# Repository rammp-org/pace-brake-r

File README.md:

# pace-brake-r
brake resistor circuit for protecting DC batteries on high power motor controllers

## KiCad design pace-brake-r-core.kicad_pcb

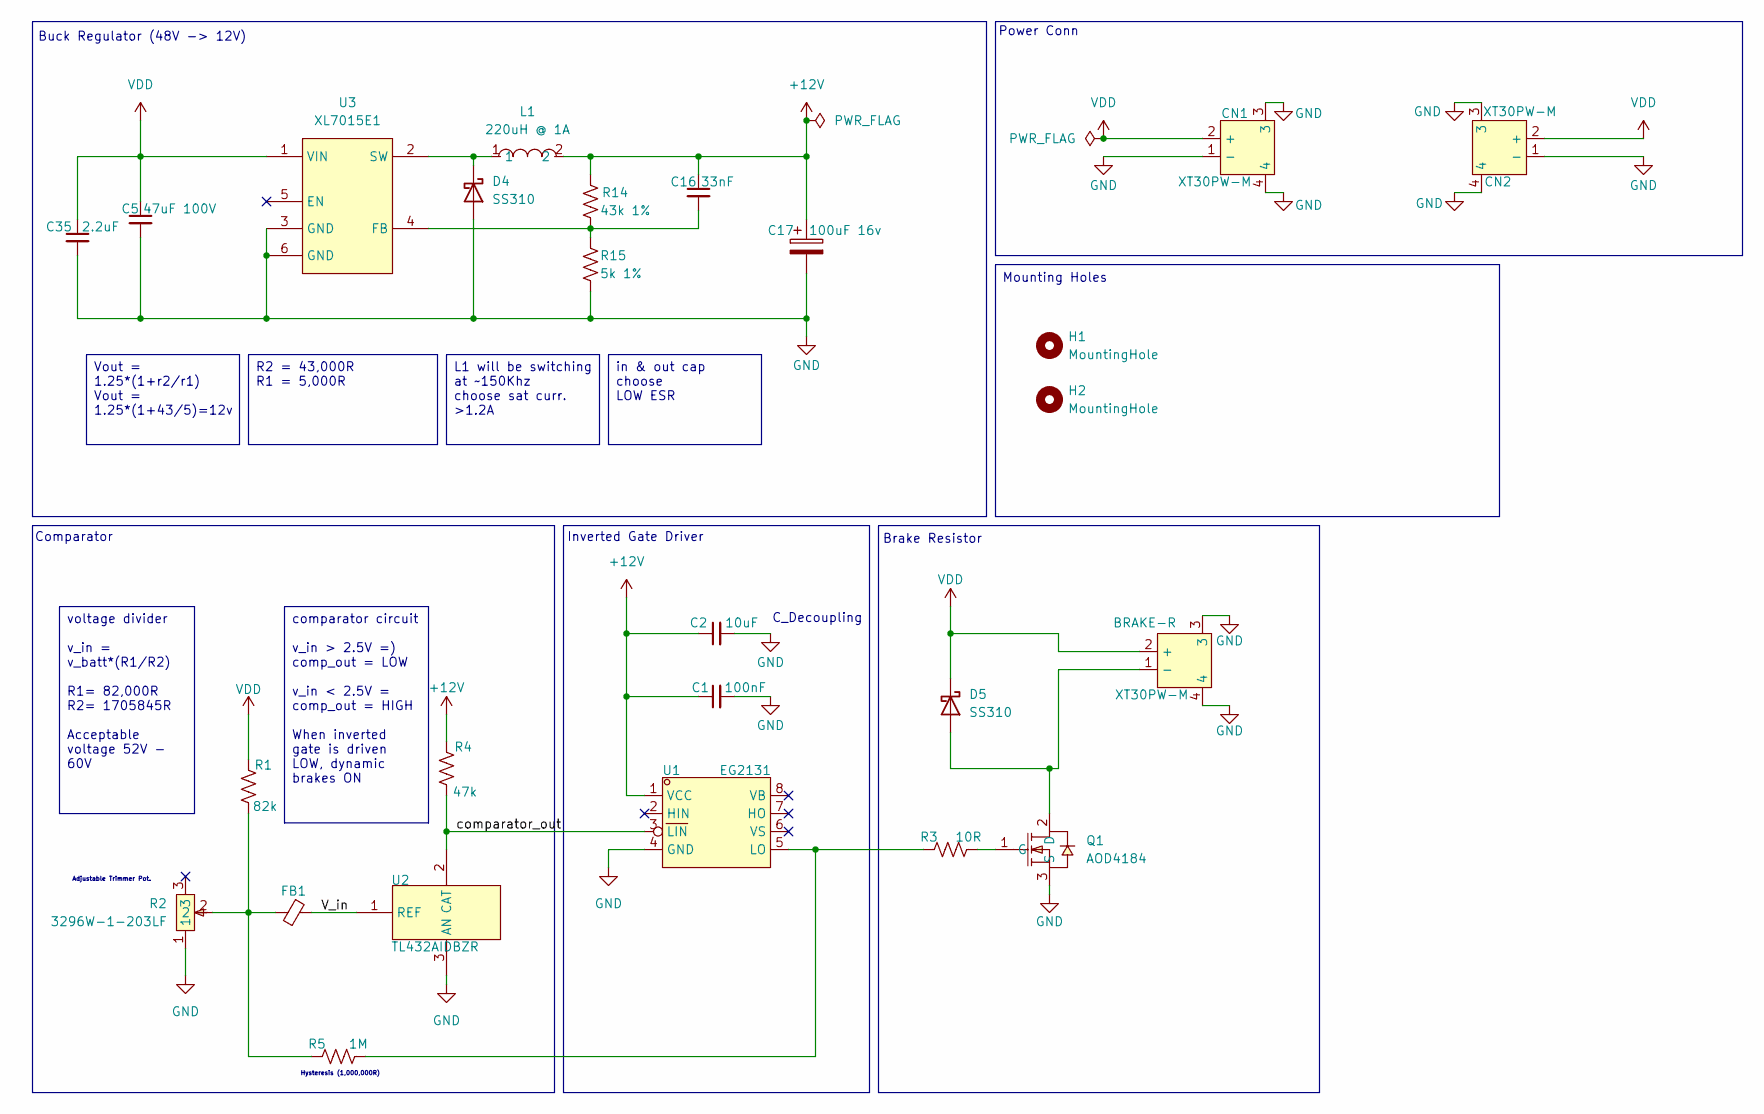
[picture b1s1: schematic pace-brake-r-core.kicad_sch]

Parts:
BRAKE-R: XT30PW-M; CONN-TH_XT30PW-M; MPN XT30PW-M30.G.Y; LCSC Part C431092
C1: 100nF; C_0402_1005Metric
C2: 10uF; C_0402_1005Metric
C5: 47uF 100V; CP_Elec_10x10
C16: 33nF; C_0402_1005Metric
C17: 100uF 16v; C_Elec_6.3x7.7; MPN EEEFPV101XAP; LCSC part C178585
C35: 2.2uF; C_1210_3225Metric
CN1, CN2: XT30PW-M; CONN-TH_XT30PW-M; MPN XT30PW-M30.G.Y; LCSC Part C431092
D4, D5: SS310; D_SMA
FB1: FerriteBead_Small; L0603
H1, H2: MountingHole; MountingHole_3.2mm_M3
L1: 220uH @ 1A; IND-TH_BD9.0-P5.00-D0.7; MPN RLB9012-221KL; LCSC Part C1330811
Q1: AOD4184; TO-252-2_L6.6-W6.1-P4.58-LS9.9-BR; MPN AOD4184-VB; LCSC Part C879026
R1: 82k; R_0402_1005Metric
R2: 3296W-1-203LF; RES-ADJ-TH_3P-L10.0-W10.0-P2.50-BL-BS; MPN 3296W-1-203LF; LCSC Part C34845
R3: 10R; R_0402_1005Metric
R4: 47k; R_0402_1005Metric
R5: 1M; R_0402_1005Metric
R14: 43k 1%; R_0402_1005Metric
R15: 5k 1%; R_0402_1005Metric
U1: EG2131; SOIC-8_L5.0-W4.0-P1.27-LS6.0-BL; MPN EG2131; LCSC Part C193777
U2: TL432AIDBZR; SOT-23-3_L2.9-W1.3-P1.90-LS2.4-BR; MPN TL432AIDBZR; LCSC Part C82720
U3: XL7015E1; TO-252-5_L6.6-W5.8-P1.27-TL; MPN XL7015E1; LCSC Part C73013

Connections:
+12V: C1.1, C2.1, C16.1, C17.1, L1.2, R4.1, R14.1, U1.1 (VCC)
GND: BRAKE-R.3, BRAKE-R.4, C1.2, C2.2, C5.2, C17.2, C35.2, CN1.1 (-), CN1.3, CN1.4, CN2.1 (-), CN2.3, CN2.4, D4.2 (A), Q1.3 (S), R2.1, R15.2, U1.4 (GND), U2.3 (AN), U3.3 (GND), U3.6 (GND); also elsewhere on the board
unnamed 2: BRAKE-R.1 (-), D5.2 (A), Q1.2 (D); also elsewhere on the board
unnamed: D4.1 (K), L1.1, U3.2 (SW)
unnamed: FB1.2, R1.2, R2.2, R5.1
unnamed: Q1.1 (G), R3.2
unnamed: R4.2, U1.3 (LIN), U2.2 (CAT)
unnamed: R3.1, R5.2, U1.5 (LO)
unnamed: FB1.1, U2.1 (REF)
unnamed: C16.2, R14.2, R15.1, U3.4 (FB)
VDD: BRAKE-R.2 (+), C5.1, C35.1, CN1.2 (+), CN2.2 (+), D5.1 (K), R1.1, U3.1 (VIN); also elsewhere on the board

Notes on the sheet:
Buck Regulator (48V -> 12V)
Power Conn
Inverted Gate Driver
C_Decoupling
Mounting Holes
Brake Resistor
Hysteresis (1,000,000R)
Comparator
Adjustable Trimmer Pot.
voltage divider v_in = v_batt*(R1/R2) R1= 82,000R R2= 1705845R Acceptable voltage 52V - 60V
in & out cap choose LOW ESR
Vout = 1.25*(1+r2/r1) Vout = 1.25*(1+43/5)=12v
comparator circuit v_in > 2.5V =) comp_out = LOW v_in < 2.5V = comp_out = HIGH When inverted gate is driven LOW, dynamic brakes ON
R2 = 43,000R R1 = 5,000R
L1 will be switching at ~150Khz choose sat curr. >1.2A

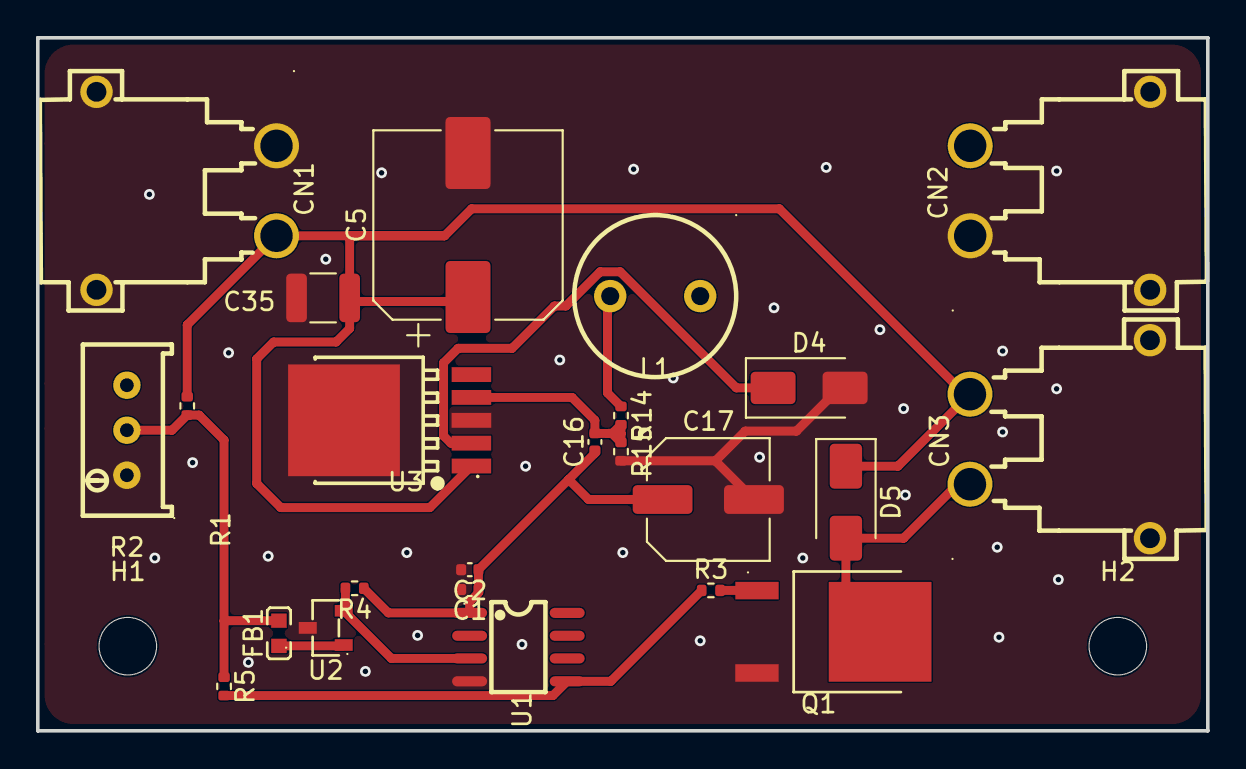
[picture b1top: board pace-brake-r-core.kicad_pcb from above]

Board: 4 copper layers, 65.0 x 38.5 mm, 26 parts (0 on the bottom side), 11 nets.

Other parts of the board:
CN3: XT30PW-M; CONN-TH_XT30PW-M

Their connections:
GND: CN3.3, CN3.4; also elsewhere on the board
unnamed 2: CN3.1 (-); also elsewhere on the board
VDD: CN3.2 (+); also elsewhere on the board
